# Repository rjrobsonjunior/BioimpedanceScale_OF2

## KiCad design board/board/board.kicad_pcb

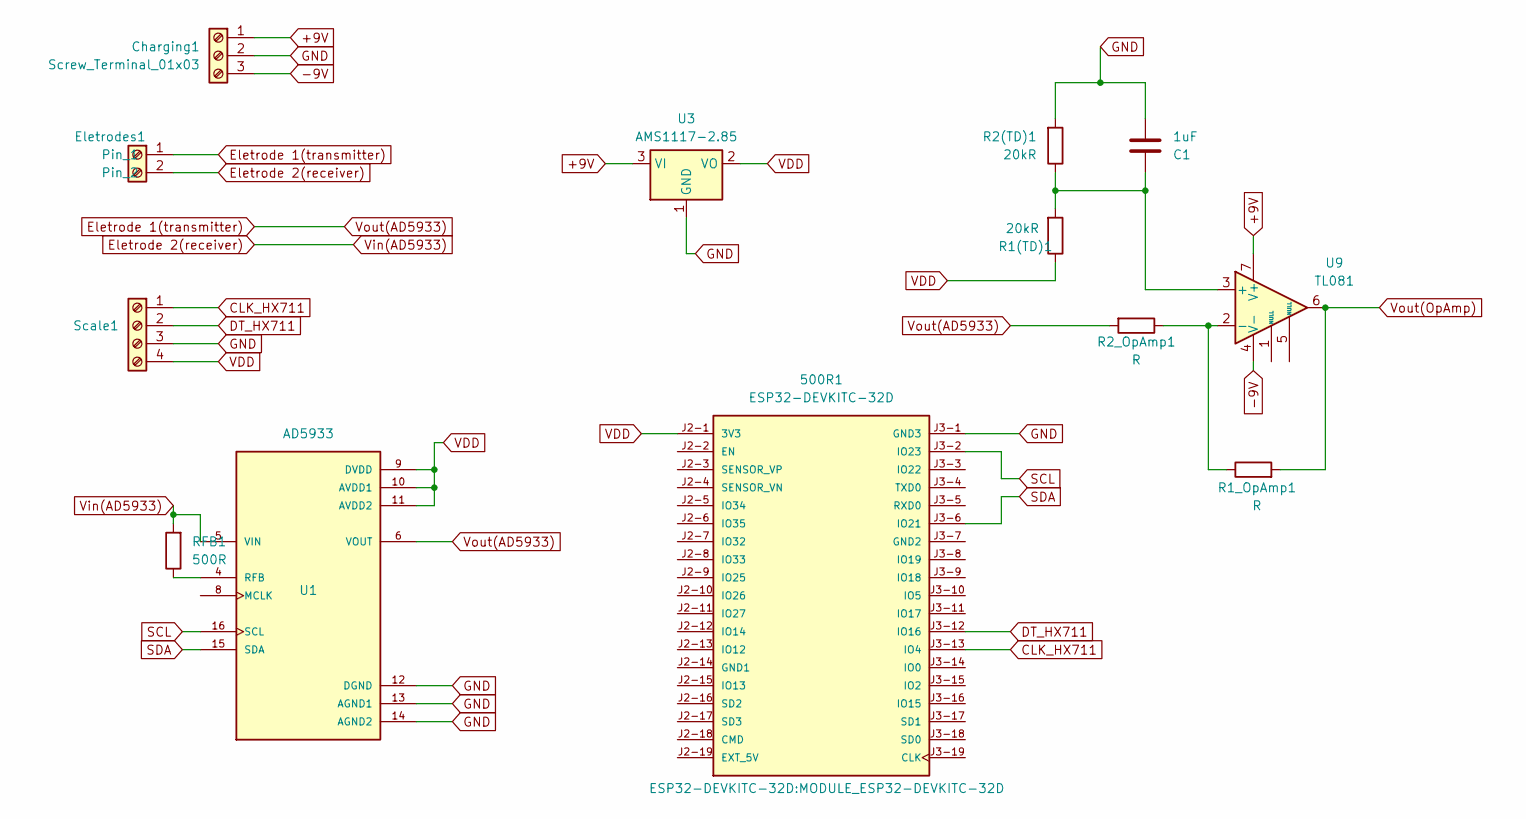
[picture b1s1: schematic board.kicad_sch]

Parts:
500R1: ESP32-DEVKITC-32D; MODULE_ESP32-DEVKITC-32D; PARTREV V4
C1: 1uF
Charging1: Screw_Terminal_01x03; TerminalBlock_4Ucon_1x03_P3.50mm_Vertical
Eletrodes1: Screw_Terminal_01x02; TerminalBlock_MetzConnect_Type011_RT05502HBWC_1x02_P5.00mm_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
R1(TD)1, R2(TD)1: 20kR; R_Axial_DIN0207_L6.3mm_D2.5mm_P7.62mm_Horizontal
R1_OpAmp1, R2_OpAmp1: R; R_Axial_DIN0207_L6.3mm_D2.5mm_P7.62mm_Horizontal
RFB1: 500R; R_Axial_DIN0207_L6.3mm_D2.5mm_P7.62mm_Horizontal
Scale1: Screw_Terminal_01x04; TerminalBlock_Xinya_XY308-2.54-4P_1x04_P2.54mm_Horizontal
U1: AD5933; SOP65P780X200-16N; PARTREV F
U3: AMS1117-2.85; SOT-223-3_TabPin2
U9: TL081; DIP-8_W7.62mm

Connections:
+9V: Charging1.1, U3.3 (VI), U9.7 (V+)
-9V: Charging1.3, U9.4 (V-)
CLK_HX711: 500R1.J3-13 (IO4), Scale1.1
DT_HX711: 500R1.J3-12 (IO16), Scale1.2
Eletrode 1(transmitter): Eletrodes1.1, R2_OpAmp1.2, U1.6 (VOUT)
Eletrode 2(receiver): Eletrodes1.2, RFB1.2, U1.5 (VIN)
GND: 500R1.J3-1 (GND3), C1.2, Charging1.2, R2(TD)1.2, Scale1.3, U1.12 (DGND), U1.13 (AGND1), U1.14 (AGND2), U3.1 (GND)
unnamed: RFB1.1, U1.4 (RFB)
unnamed: C1.1, R1(TD)1.2, R2(TD)1.1, U9.3 (+)
unnamed: R1_OpAmp1.1, R2_OpAmp1.1, U9.2 (-)
SCL: 500R1.J3-2 (IO23), U1.16 (SCL)
SDA: 500R1.J3-6 (IO21), U1.15 (SDA)
VDD: 500R1.J2-1 (3V3), R1(TD)1.1, Scale1.4, U1.9 (DVDD), U1.10 (AVDD1), U1.11 (AVDD2), U3.2 (VO)
Vout(OpAmp): R1_OpAmp1.2, U9.6

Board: 2 copper layers, 12 parts (0 on the bottom side), 14 nets, no tracks yet.

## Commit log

2024-09-22 add blog boilerplate
2024-09-22 add readme
2024-09-22 add hugo theme
2024-09-22 add members to Team page
2024-09-22 add template for sw and fw
2024-09-22 blog: add schedule page
2024-09-22 blog: update readme
2024-09-22 blog: add template post
2024-09-22 add hugo deployment config file
2024-09-22 rm gitmodules sw/app
2024-09-23 test changing github action working directory
2024-09-23 aaaaaaaaaaaaaa
2024-09-23 mental breakdown
2024-09-23 mental breakdown 2.0
2024-09-23 that didnt work
2024-09-24 remove app/ to get rid of submodule
2024-09-24 blog: change blog url
2024-09-24 test
2024-09-24 fixing action
2024-09-24 trying to fix this piece of crap. WHY DO I HAVE TO PUSH THESE COMMITS JUST TO TEST THE ACTION
2024-09-24 blog: move images to assets directory
2024-09-24 blog: maybe fix images not showing
2024-09-24 blog: fix this time?
2024-09-24 blog: 10000th time is the charm
2024-09-24 100001th time
2024-09-24 teste
2024-09-24 test2
2024-09-25 blog: add theme source code directly to repo instead of submodule
2024-09-25 blog: change assets paths to relative. TEST
2024-09-25 test relURL
2024-10-02 aaaaaaa
2024-10-02 change baseurl
2024-10-03 checkpoint
2024-10-03 remove github actions
2024-10-04 conserta o nome do meu mano damasceno
2024-10-04 update blog public
2024-11-05 update blog
2024-11-05 blog: remove entry cronograma
2024-11-05 blog: update Home
2024-11-05 blog: update .gitignore
2024-11-05 blog: delete pulic directory
2024-11-06 update footer
2024-11-07 react native & sqlite exploration
2024-11-07 app: add date_of_birth to user table
2024-11-07 fw base
2024-11-10 AD5933 tests
2024-11-12 app: sync some stuff. Still testing
2024-11-13 app: sqlite database creation working
2024-11-19 tested HX711
2024-11-26 app: implement storage as singleton
2024-11-26 tomara que funcione 2.0
2024-11-26 remove me later
2024-11-26 jesus tomara que funcione
2024-11-26 blog: remove team.md
2024-11-26 blog: add .gitmodules
2024-11-26 blog: add .gitignore
2024-11-28 change url
2024-11-28 blog: move images and pdfs to static
2025-02-09 HX711 e envio de peso lido via bluetooth
2025-02-09 biblioteca de leitura de peso no /fw
2025-02-09 lib de conexao BLE no /fw
2025-02-09 teste uso libs do hx e ble
2025-02-09 implementar leitura de mensagem via BLE
2025-02-09 lib para leitura do AD5933
2025-02-09 rotina completa BIA
2025-02-15 ad5933 test
2025-02-15 ajustes 15/02
2025-02-19 ajuste de str enviada e fator de ganho
